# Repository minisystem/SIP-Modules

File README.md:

SIP-Modules
===========

Analogue SIP modules

Single Inline Pin [SIP] Package Modules for Analogue Synthesizer Design
===============================================================

******************************
IMPORTANT!- READ THIS FIRST!!!
*************************************************************************************************************
THESE REPOSITORIES ARE A MESS RIGHT NOW BECAUSE OF MY PREVIOUS AD HOC VERSION CONTROL
I will eventually tidy them up but at the moment I don't know which are the latest and fully correct versions 
*************************************************************************************************************

What are these?
===============

These are designs for modules that make up the bulidng blocks of an analogue synthesizer. They were inspired 
by the original Curtis Electromusic (CEM) chips used in dozens of 70s and 80s synthesizer designs. They are *NOT* 
electronically equivalent to the original CEM chips. They were designed to be compact modules for building 
a polyphonic analogue synthesizer. They use SMT parts but are designed for hand soldering. As there are parts on both sides of the board a substantial redesign might be required for automated assmebly by a pick-and-place assembly service.

VCO SIP
=======
This is an analogue Voltage Controlled Oscillator (VCO) module in a 30 mm x 18 mm 12 pin SIP package.
It is a classic SAW core design derived from the Terry Michaels/Mikulik/Electronotes/ASM-1 circuit. It employs 
waveshapers from George Hearn's HMVCO1c design, with modifications to limit output levels to 10V pp. Other
changes from the original Electronotes design include elimination of the linear FM input and swapping the CA3140 
integrator for the cheaper LF351. It uses an inexpensive BCM847 NPN matched transistor pair in contrast
to the super matched pairs (LS318, LM394, SSM2210, etc) called for in other SAW core designs.

VCF-VCA SIP
===========
This is a 4 pole LM13700 OTA-based Voltage Controlled Filter (VCF) in a 40 mm x 18 mm 10 pin SIP package.  It is derived from Roland filter designs based around the IR3109 quad OTA filter. Voltage controlled resonance is implemented with an LM13700 OTA cell and the spare OTA is used for a Voltage Controlled Amplifier (VCA), thus combining two functions into one module, similiar to the Roland D80017A VCF-VCA module used in the Juno 106.

EG ADSR SIP
===========
This is a voltage controlled Envelope Generator (EG) with Attack, Decay, Sustain and Release stages in a 30 mm x 18 mm 10 pin SIP package. It is derived from similar designs by Massimo Ischia and Scott Rider (OldCrow) with modifications to respond to 0-10V control voltages and to produce a 0-10V output.

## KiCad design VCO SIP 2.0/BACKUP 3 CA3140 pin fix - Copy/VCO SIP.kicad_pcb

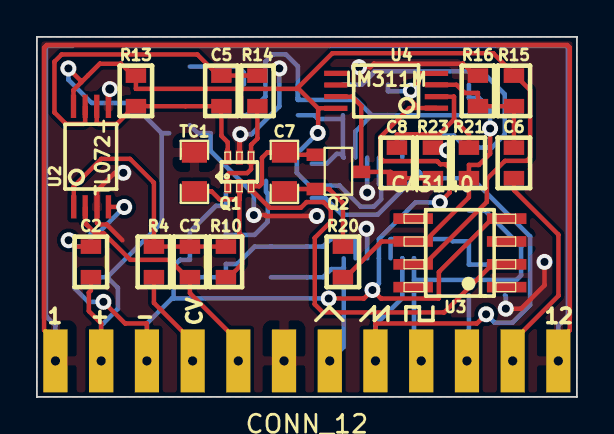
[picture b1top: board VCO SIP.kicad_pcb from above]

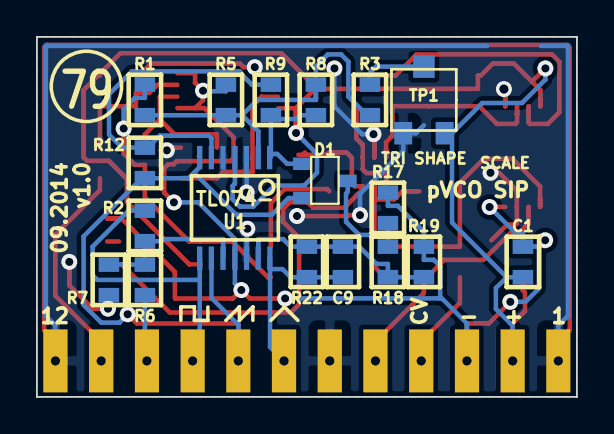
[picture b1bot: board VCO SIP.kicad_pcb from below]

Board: 2 copper layers, 30.0 x 20.0 mm, 40 parts (18 on the bottom side), 28 nets.

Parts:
C1, C2: 100n; SM0603-JRL
C3, C5, C6, C9: 100p; SM0603-JRL
C7: 2.2n 1%; SM0805-HAND
C8: 18p; SM0603-JRL
D1: BAV70; SOT23-JRL
P1: CONN_12; CONN_12X_0100_SMD_THRUHOLE
Q1: BCM847; SOT363-JRL
Q2: MMBF4391LT1G; SOT23-JRL
R1, R6, R14, R16: 10K; SM0603-JRL
R2, R3: 1M; SM0603-JRL
R4: 91K; SM0603-JRL
R5, R7, R9, R10, R12, R19: 56K; SM0603-JRL
R8: 39K; SM0603-JRL
R13: 1.5M; SM0603-JRL
R15: 20K; SM0603-JRL
R17, R18, R21: 15K; SM0603-JRL
R20: 680; SM0603-JRL
R22: 33K; SM0603-JRL
R23: 3.3K; SM0603-JRL
TC1: 1K 3300ppm/K; SM0805-HAND
TP1: 100K; PVG3
U1: TL074-; TSSOP-14
U2: TL072-; TSSOP8-JRL
U3: CA3140; SOIC-8-JRL
U4: LM311M; TSSOP8-JRL

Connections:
0V: P1.1, P1.6, P1.12, Q1.5, R7.2, R16.1, R23.1, TC1.1, TP1.3, U1.3, U1.5, U1.12, U2.3, U2.5, U3.3
+VCC: C1.1, C2.1, P1.2, R13.2, R15.2, TP1.1, U1.4, U2.8, U3.7, U4.8
-VCC: C1.2, C2.2, P1.3, R5.1, R17.1, R19.1, U1.11, U2.4, U3.4, U4.1, U4.4
/TRI_SHAPE: R3.1, TP1.2
unnamed: C3.1, R4.2, R10.1, U2.1
unnamed: C5.1, Q1.6, R13.1, U2.6
unnamed: C5.2, R14.1, U2.7
unnamed: C6.2, R15.1, R16.2, U4.3
unnamed: C7.1, Q1.3, Q2.2, U3.2
unnamed: C7.2, Q2.1, R20.1
unnamed: C8.1, R21.1, U4.2
unnamed: C8.2, Q2.3, R23.2, U4.7
unnamed: C9.1, R18.2, R19.2, R22.1, U1.13
unnamed: D1.2, R8.2, R9.1, U1.1
unnamed: D1.3, R17.2, R18.1
unnamed: Q1.1, Q1.4, R14.2
unnamed: Q1.2, R10.2, TC1.2
unnamed: R1.2, R3.2, R5.2, R8.1, U1.2
unnamed: R2.2, R6.1, R7.1, U1.10
unnamed: R9.2, R12.1, U1.6
PITCH_CV: C3.2, P1.5, U2.2
PULSE: P1.9, R2.1, U1.8
PWM_CV: P1.10, R6.2
RAMP: R1.1, R20.2, R21.2, U3.6
SAW: D1.1, P1.8, R12.2, U1.7, U1.9
SCALE: P1.4, R4.1
SYNC: C6.1, P1.11
TRI: C9.2, P1.7, R22.2, U1.14

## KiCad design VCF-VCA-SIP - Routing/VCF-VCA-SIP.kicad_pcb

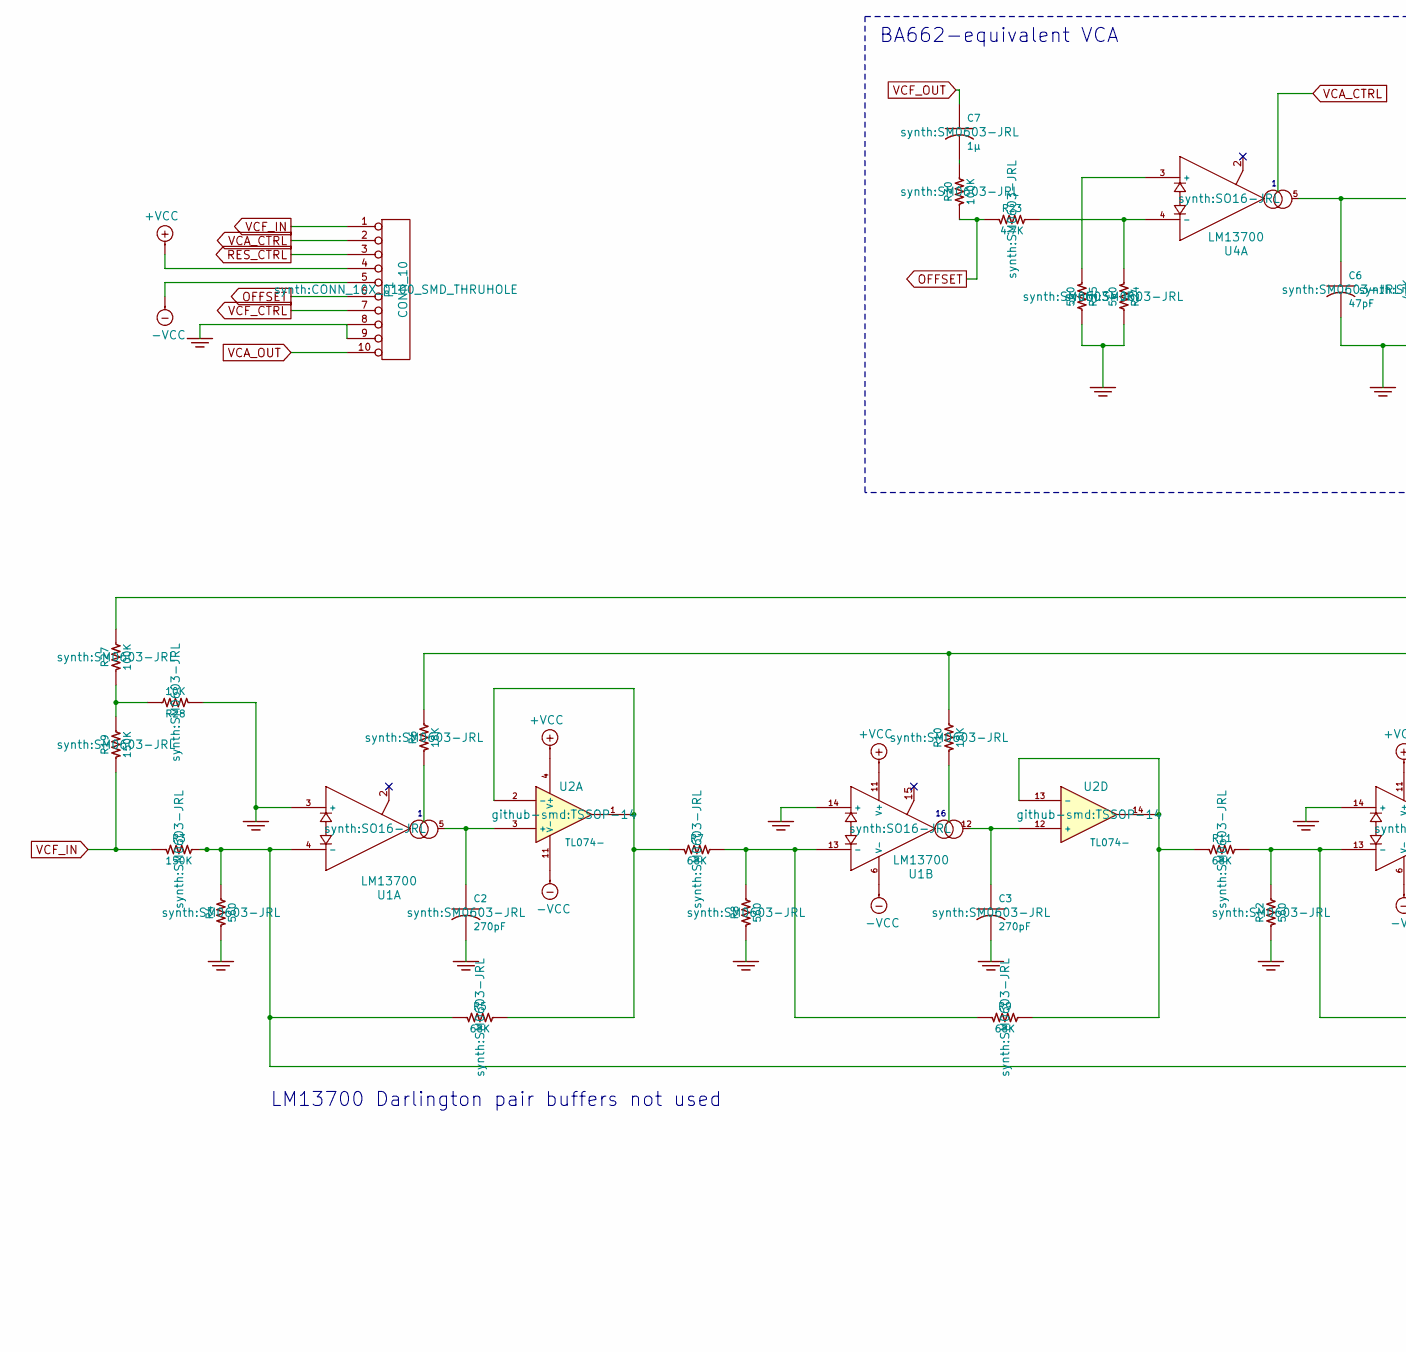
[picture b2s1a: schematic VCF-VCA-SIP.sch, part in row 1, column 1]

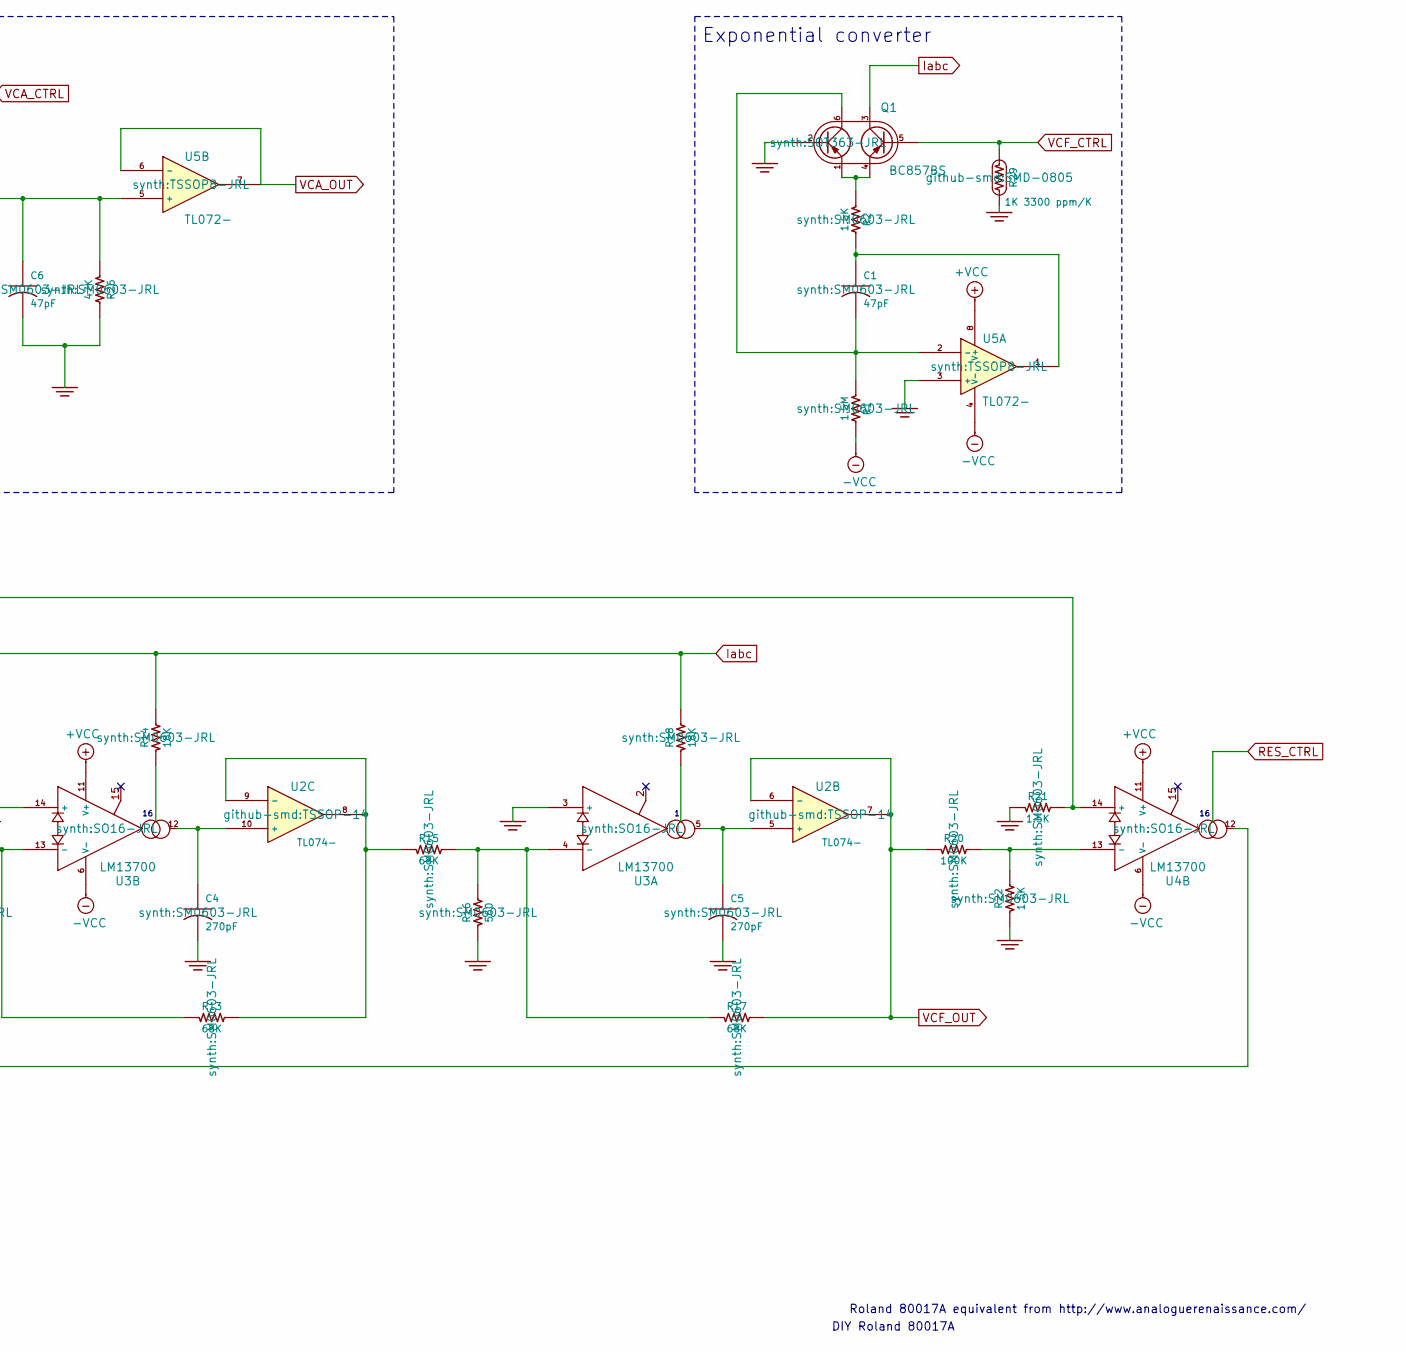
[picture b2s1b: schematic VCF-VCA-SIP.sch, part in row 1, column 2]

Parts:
C1, C6: 47pF; SM0603-JRL
C2, C3, C4, C5: 270pF; SM0603-JRL
C7: 1μ; SM0603-JRL
P1: CONN_10; CONN_10X_0100_SMD_THRUHOLE
Q1: BC857BS; SOT363-JRL
R1: 1.5M; SM0603-JRL
R2, R21, R22: 1.5K; SM0603-JRL
R3, R19: 150K; SM0603-JRL
R4, R8, R12, R16, R24, R25: 560; SM0603-JRL
R5, R7, R9, R11, R13, R15, R17: 68K; SM0603-JRL
R6, R10, R14, R18: 18K; SM0603-JRL
R20, R27, R30: 100K; SM0603-JRL
R23: 4.7K; SM0603-JRL
R26: 47K; SM0603-JRL
R28: 10K; SM0603-JRL
R29: 1K 3300 ppm/K; SMD-0805
U1, U3, U4: LM13700; SO16-JRL
U2: TL074-; TSSOP-14
U5: TL072-; TSSOP8-JRL

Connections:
+VCC: P1.4, U1.11 (V+), U2.4 (V+), U3.11 (V+), U4.11 (V+), U5.8 (V+)
-VCC: P1.5, R1.2, U1.6 (V-), U2.11 (V-), U3.6 (V-), U4.6 (V-), U5.4 (V-)
GND: C2.2, C3.2, C4.2, C5.2, C6.2, P1.8, P1.9, Q1.2 (B1), R4.1, R8.1, R12.1, R16.1, R21.2, R22.1, R24.2, R25.2, R26.2, R28.1, R29.2, U1.3 (+), U1.14 (+), U3.3 (+), U3.14 (+), U5.3 (+)
Iabc: Q1.3 (C2), R6.2, R10.2, R14.2, R18.2
unnamed: C1.1, R2.2, U5.1
unnamed: C1.2, Q1.6 (C1), R1.1, U5.2 (-)
unnamed: C2.1, U1.5, U2.3 (+)
unnamed: C3.1, U1.12, U2.12 (+)
unnamed: C4.1, U2.10 (+), U3.12
unnamed: C5.1, U2.5 (+), U3.5
unnamed: C6.1, R26.1, U4.5, U5.5 (+)
unnamed: C7.2, R30.2
unnamed: Q1.1 (E1), Q1.4 (E2), R2.1
unnamed: R3.2, R4.2, R5.2, U1.4 (-), U4.12
unnamed: R5.1, R7.2, U2.1, U2.2 (-)
unnamed: R6.1, U1.1
unnamed: R7.1, R8.2, R9.2, U1.13 (-)
unnamed: R10.1, U1.16
unnamed: R11.1, R12.2, R13.2, U3.13 (-)
unnamed: R9.1, R11.2, U2.13 (-), U2.14
unnamed: R13.1, R15.2, U2.8, U2.9 (-)
unnamed: R14.1, U3.16
unnamed: R15.1, R16.2, R17.2, U3.4 (-)
unnamed: R18.1, U3.1
unnamed: R19.2, R27.1, R28.2
unnamed: R20.1, R22.2, U4.13 (-)
unnamed: R21.1, R27.2, U4.14 (+)
unnamed: R23.1, R24.1, U4.4 (-)
unnamed: R25.1, U4.3 (+)
OFFSET: P1.6, R23.2, R30.1
RES_CTRL: P1.3, U4.16
VCA_CTRL: P1.2, U4.1
VCA_OUT: P1.10, U5.6 (-), U5.7
VCF_CTRL: P1.7, Q1.5 (B2), R29.1
VCF_IN: P1.1, R3.1, R19.1
VCF_OUT: C7.1, R17.1, R20.2, U2.6 (-), U2.7

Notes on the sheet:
LM13700 Darlington pair buffers not used
BA662-equivalent VCA
Exponential converter
DIY Roland 80017A
Roland 80017A equivalent from http://www.analoguerenaissance.com/

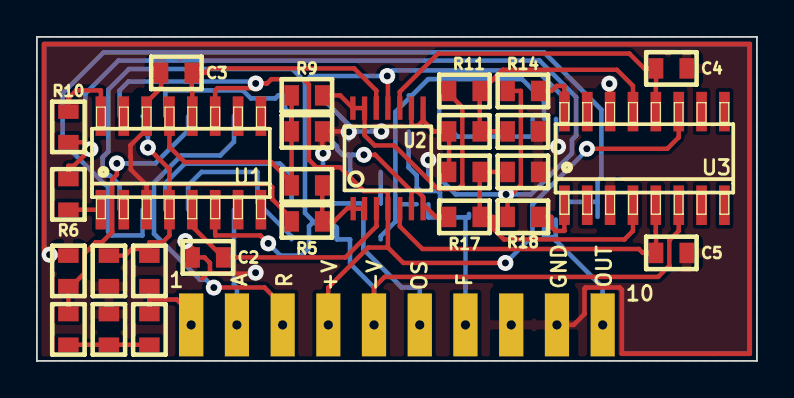
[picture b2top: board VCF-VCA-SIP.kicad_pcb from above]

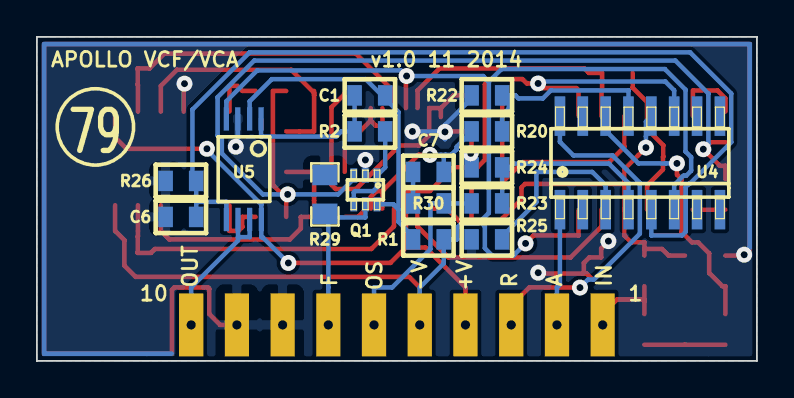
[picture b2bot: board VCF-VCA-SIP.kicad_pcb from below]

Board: 2 copper layers, 40.0 x 18.0 mm, 44 parts (16 on the bottom side), 36 nets.

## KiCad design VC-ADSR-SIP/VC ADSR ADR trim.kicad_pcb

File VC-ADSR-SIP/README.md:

Voltage Controlled ADSR Envelope Generator
==========================================

This is a voltage controlled Envelope Generator (EG) with Attack, Decay, Sustain and Release stages in a 30 mm x 18 mm 12 pin SIP package. It is derived from similar designs by Massimo Ischia and Scott Rider (OldCrow) with modifications to respond to 0-10V control voltages and to produce a 0-10V output.

Massimo Ischia's version:
http://digilander.libero.it/ismsynth/vc-adsr-1.2.jpg

Scott Rider's version:
http://www.muffwiggler.com/forum/viewtopic.php?p=1151245
(scroll down for schematic in thread)

Notes
=====

Ideally, I'd like to eliminate the trimmers for Attack and Decay/Release times. I tried doing this in an early revision but needed to tweak the resistor values more than I expected so reverted to trimmers. However, in subsequent revisions I've hardly needed to make any adjustments at all. A 0603 or 0805 resistor should be able to bridge the T1 and T2 footprints.

Q1's schematic symbol has a pin numbering that swapped the emitter (pin 1) and base (pin 2) when used with the default SOT23 footprint. I fixed this by swapping the pad numbers on the SOT23 footprint module, but this change applies to *this project only*.

This project was created in Kicad 4022 but routed in 5112 using the CERN push and shove router. This means that the CvPcb footprint association uses the legacy library format and not the new library table format. I haven't tried to do the conversion yet.

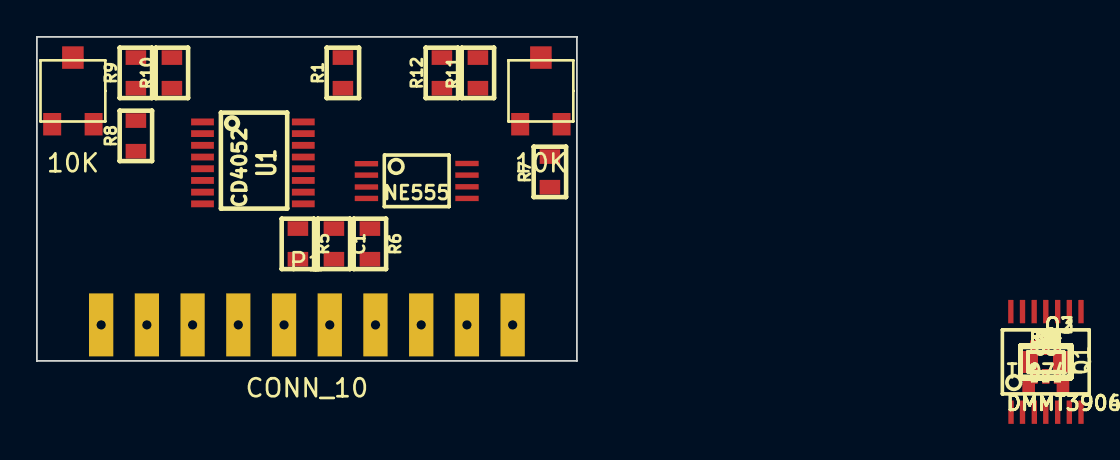
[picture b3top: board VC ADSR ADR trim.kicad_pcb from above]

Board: 2 copper layers, 30.0 x 18.0 mm, 39 parts (0 on the bottom side), 32 nets, no tracks yet.

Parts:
C1, C3, C6, C7: 100n; SM0603-JRL
C4: 100p; SM0603-JRL
C5: 100n**; SM0603-JRL
P1: CONN_10; CONN_10X_0100_SMD_THRUHOLE
Q1: 2N3904; SOT23
Q2: DMMT3904; SOT363-JRL
Q3: DMMT3906; SOT363-JRL
R1: 15K; SM0603-JRL
R2, R18, R24: 100K; SM0603-JRL
R3: 33K; SM0603-JRL
R4: 330K; SM0603-JRL
R5: 22K; SM0603-JRL
R6, R22, R23: 10K; SM0603-JRL
R7, R8: 82K*; SM0603-JRL
R9, R11, R15: 2.2K; SM0603-JRL
R10, R12: 270K; SM0603-JRL
R13: 150K; SM0603-JRL
R14: 3.3K**; SM0603-JRL
R16, R17, R19, R20: 47K; SM0603-JRL
R21: 1K; SM0603-JRL
T1, T2: 10K; PVG3
U1: CD4052; TSSOP16
U2: NE555; TSSOP8-JRL
U3: TL074-; TSSOP14

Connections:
+12V: C3.1, C6.1, P1.1, R1.1, R5.2, R6.1, R14.2, R22.1, U1.16, U2.4, U2.8, U3.4
-12V: C7.2, P1.3, R4.2, R10.1, R12.1, U3.11
ATTACK: P1.9, R7.1
DECAY: P1.2, U1.1
ENV OUT: P1.4, R21.2
GATE: P1.10, R2.1, R3.2
GND: C3.2, C6.2, C7.1, P1.8, Q1.1, Q2.2, Q3.1, R2.2, R9.1, R11.1, R20.2, R23.1, U1.2, U1.6, U1.7, U1.8, U1.11, U1.14, U2.1, U3.10, U3.12
INV OUT: P1.5, R24.2, U3.1
unnamed: Q1.2, R3.1, R4.1
unnamed: C5.1, R18.1, R19.2, R21.1, U2.6, U3.14
unnamed: C5.2, Q2.3, Q3.3, U3.13
unnamed: C1.1, Q1.3, R5.1, U1.10
unnamed: R14.1, U2.5
unnamed: C1.2, R6.2, U2.2
unnamed: R22.2, R23.2, U3.3
unnamed: C4.1, R15.1, U3.8
unnamed: R13.2, R16.1, U3.7
unnamed: R17.1, U1.13
unnamed: R17.2, R20.1, U3.5
unnamed: R16.2, R19.1, U3.6
unnamed: R1.2, U1.15
unnamed: R8.2, T2.1
unnamed: R7.2, T1.1
unnamed: R18.2, R24.1, U3.2
unnamed: Q2.4, Q2.5, Q3.4, Q3.5, R15.2
unnamed: R8.1, U1.3
unnamed: U1.9, U2.3
unnamed: Q2.1, R11.2, R12.2, T1.2, T1.3
unnamed: Q3.2, R9.2, R10.2, T2.2, T2.3
unnamed: C4.2, Q2.6, Q3.6, R13.1, U3.9
RELEASE: P1.7, U1.4, U1.5
SUSTAIN: P1.6, U1.12

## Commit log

2014-12-27 First add
2015-01-28 changed Q1 footprint E and B were swapped
2015-01-28 gerbers with fixed Q1 footprint plotted
2015-01-28 changed VC ADSR folder to name without spaces
2015-01-28 cleaned up VC ADSR directory
2015-01-28 added readme for VC-ADSR-SIP
2015-03-02 updated schematic PDF
